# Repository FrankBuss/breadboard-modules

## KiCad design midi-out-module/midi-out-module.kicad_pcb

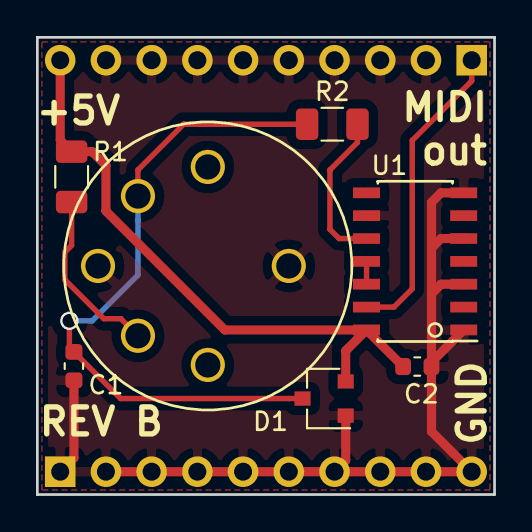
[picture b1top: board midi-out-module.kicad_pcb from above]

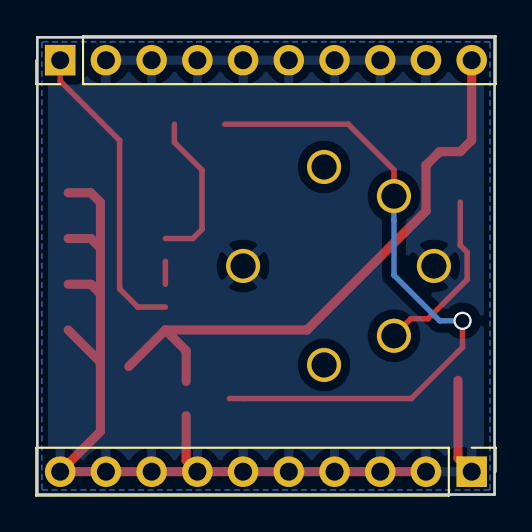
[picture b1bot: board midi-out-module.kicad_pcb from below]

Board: 2 copper layers, 25.4 x 25.4 mm, 9 parts (2 on the bottom side), 7 nets.

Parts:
C1: 1n; C_0603_1608Metric
C2: 100n; C_0603_1608Metric
D1: BAV99; SC-59
J1: DIN-5-GND; DIN_CUI_SD-50BV
J2, J3: Conn_01x10_Male; PinHeader_1x10_P2.54mm_Vertical
R1, R2: 220; R_1206_3216Metric
U1: 74LS14; SOIC-14_3.9x8.7mm_P1.27mm

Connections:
GND: C1.2, C2.2, D1.1, J1.2, J1.6, J2.1, J2.2, J2.3, J2.4, J2.5, J2.6, J2.7, J2.8, J2.9, J2.10, J3.2, J3.3, J3.4, J3.5, J3.6, J3.7, J3.8, J3.9, U1.1, U1.3, U1.5, U1.7, U1.9
unnamed: C1.1, D1.3, J1.5, R2.1
unnamed: J1.4, R1.2
unnamed: J3.1, U1.13
unnamed: R2.2, U1.10
unnamed: U1.11, U1.12
VCC: C2.1, D1.2, J3.10, R1.1, U1.14

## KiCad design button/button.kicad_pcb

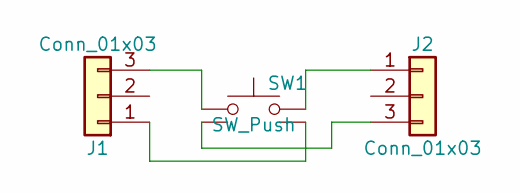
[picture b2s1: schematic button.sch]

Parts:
J1, J2: Conn_01x03; PinHeader_1x03_P2.54mm_Vertical
SW1: SW_Push; B3F-through-hole

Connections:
unnamed: J1.1, SW1.3
unnamed: J1.3, SW1.1
unnamed: J2.1, SW1.4
unnamed: J2.3, SW1.2

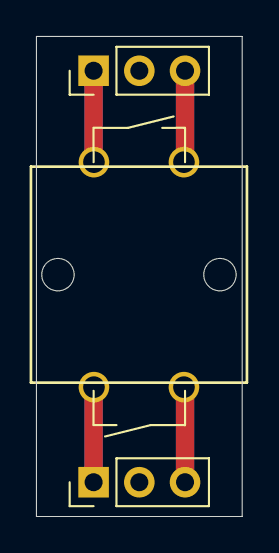
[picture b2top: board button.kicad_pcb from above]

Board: 2 copper layers, 11.4 x 26.7 mm, 3 parts (0 on the bottom side), 4 nets.

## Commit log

2019-05-06 scaled images
2019-05-16 new MIDI out module
